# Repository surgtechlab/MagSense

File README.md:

# MagSense

Code and Library for the Leeds Surgical Technologies Lab - Magnetic Sensing Platform

Maintained by Pete Culmer

Contributions from:
******************************
Chris Adams
Max Houghton
Pete Culmer
Belquis Haider

Links:
******************************
This owes a debt to the more general purpose MLX90393 driver
https://github.com/tedyapo/arduino-MLX90393

TODO LIST
******************************
Add Bluetooth communication
 
Simplify I2C code
  ***Use wrapper function to provide a single interface to the mutliple I2C buses - for the commands below:
  Wire.beginTransmission(_I2CAddress);
  Wire.write(0x80)
  Wire.endTransmission()
  Wire.requestFrom(_I2CAddress, 1);
  Wire.available()
  Wire.read();

Add handshaking and commands to I2C comms
  Start/stop/reset/ack packet etc.
  
Improve error checking of chip configuration (check registers after config)

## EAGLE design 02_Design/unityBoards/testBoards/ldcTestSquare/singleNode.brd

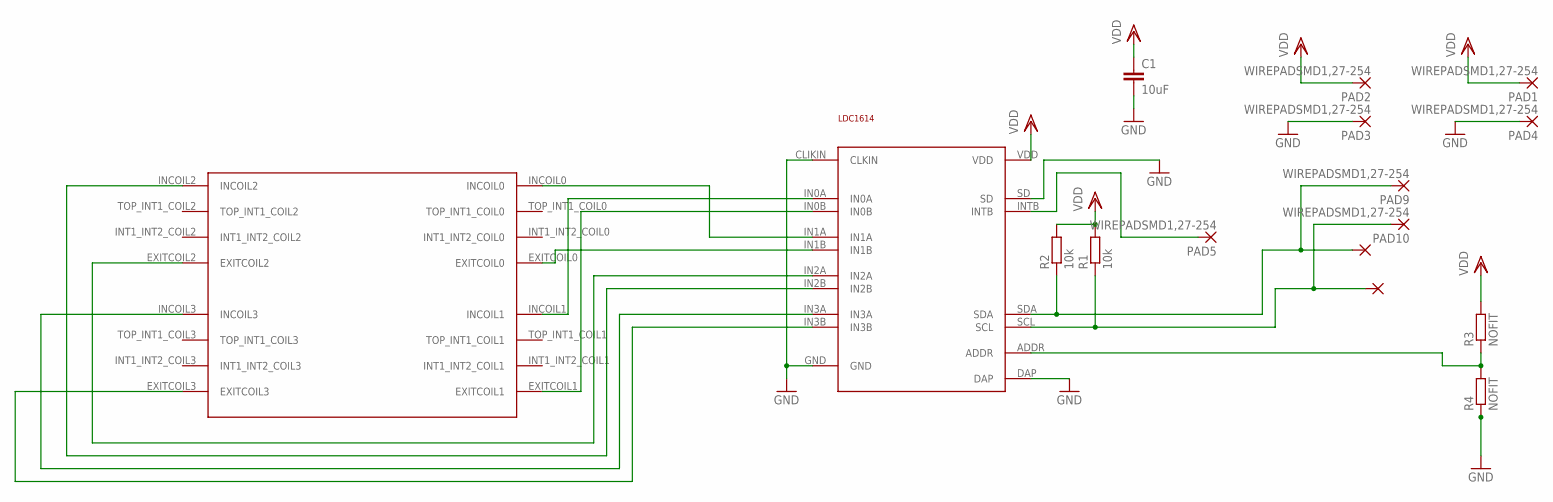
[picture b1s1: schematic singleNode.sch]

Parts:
C1: 10uF; C0402
PAD1, PAD2, PAD3, PAD4, PAD5, PAD6, PAD7, PAD9, PAD10: WIREPADSMD1,27-254; SMD1,27-2,54
R1, R2: 10k; R0402
R3, R4: NOFIT; R0201
U1: LDC1614; WQFN-16
U$2: FATSQUARE_GROUP; FAT_SQUARE

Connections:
ADDR: R3.1, R4.2, U1.ADDR
GND: C1.2, PAD3.1, PAD4.1, R4.1, U1.CLIKIN (CLKIN), U1.DAP, U1.GND, U1.SD
INTRPT: PAD5.1, U1.INTB
unnamed: U1.IN1A, U$2.INCOIL0
unnamed: U1.IN1B, U$2.EXITCOIL0
unnamed: U1.IN0A, U$2.INCOIL1
unnamed: U1.IN0B, U$2.EXITCOIL1
unnamed: U1.IN2A, U$2.EXITCOIL2
unnamed: U1.IN2B, U$2.INCOIL2
unnamed: U1.IN3A, U$2.INCOIL3
unnamed: U1.IN3B, U$2.EXITCOIL3
SCL: PAD7.1, PAD10.1, R1.1, U1.SCL
SDA: PAD6.1, PAD9.1, R2.1, U1.SDA
VDD: C1.1, PAD1.1, PAD2.1, R1.2, R2.2, R3.2, U1.VDD

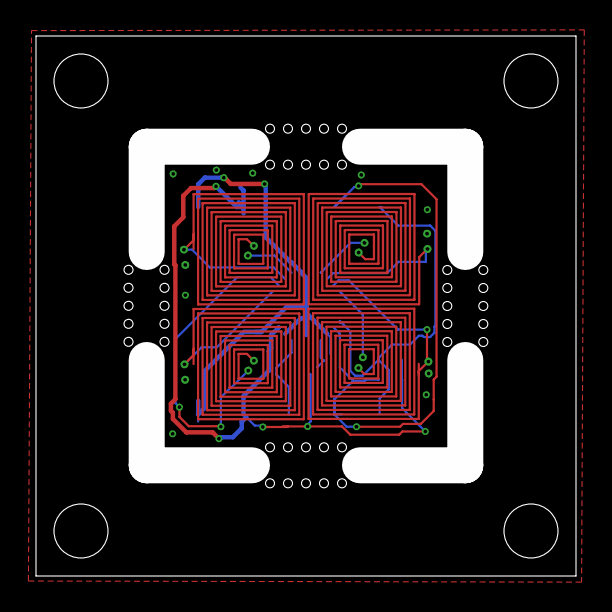
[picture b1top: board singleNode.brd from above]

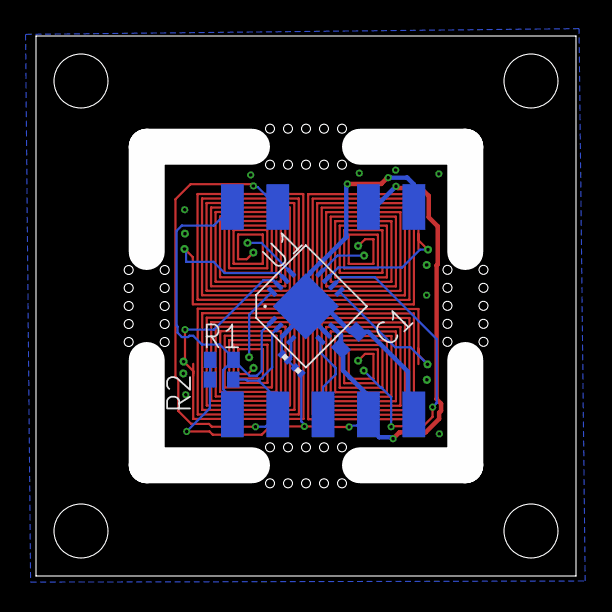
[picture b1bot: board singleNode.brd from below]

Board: 4 copper layers, 30.0 x 30.0 mm, 16 parts (15 on the bottom side), 14 nets.

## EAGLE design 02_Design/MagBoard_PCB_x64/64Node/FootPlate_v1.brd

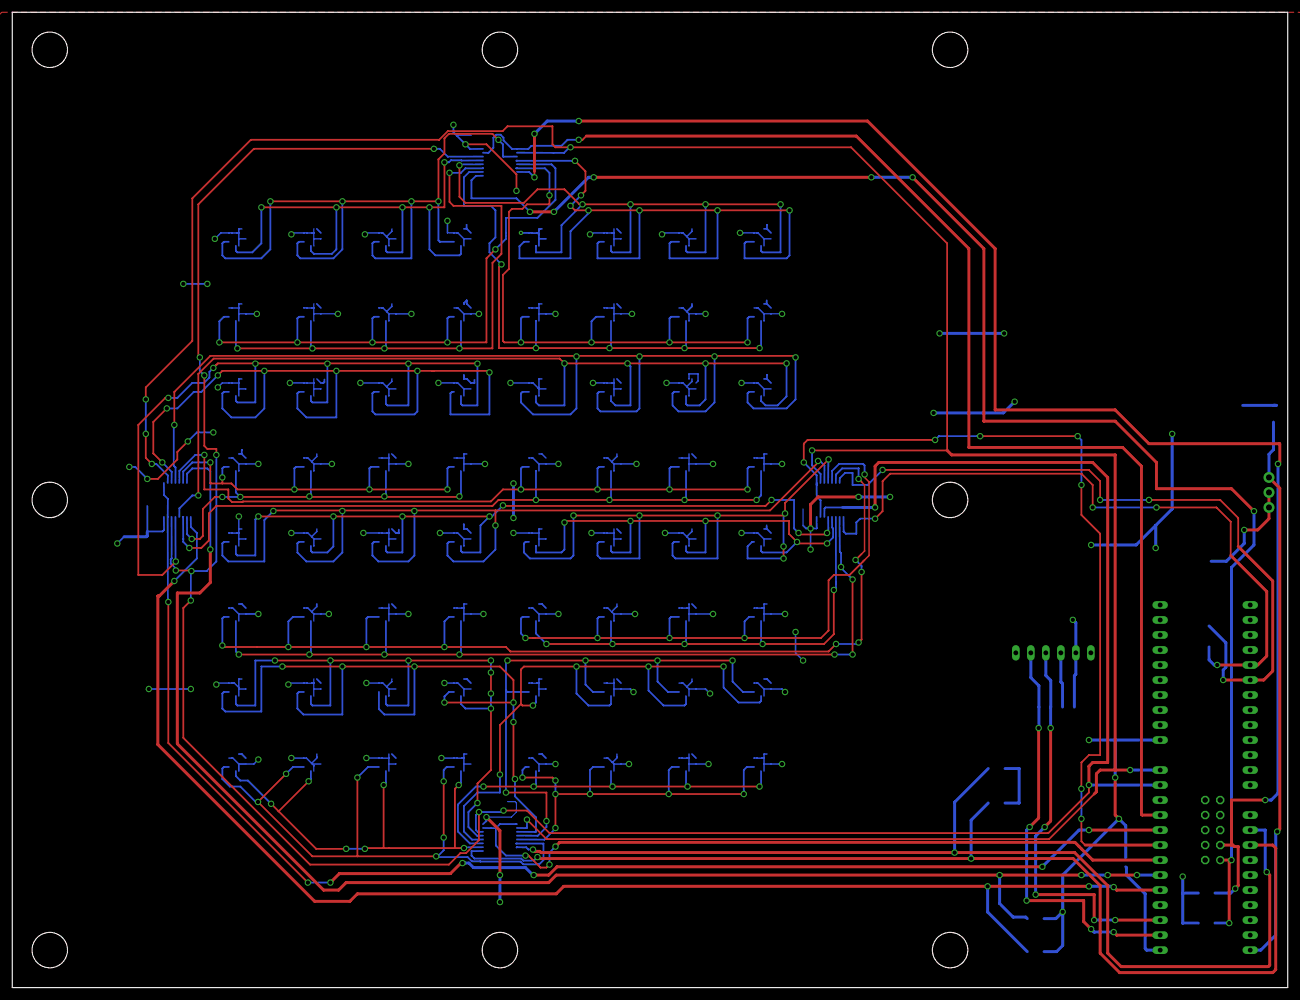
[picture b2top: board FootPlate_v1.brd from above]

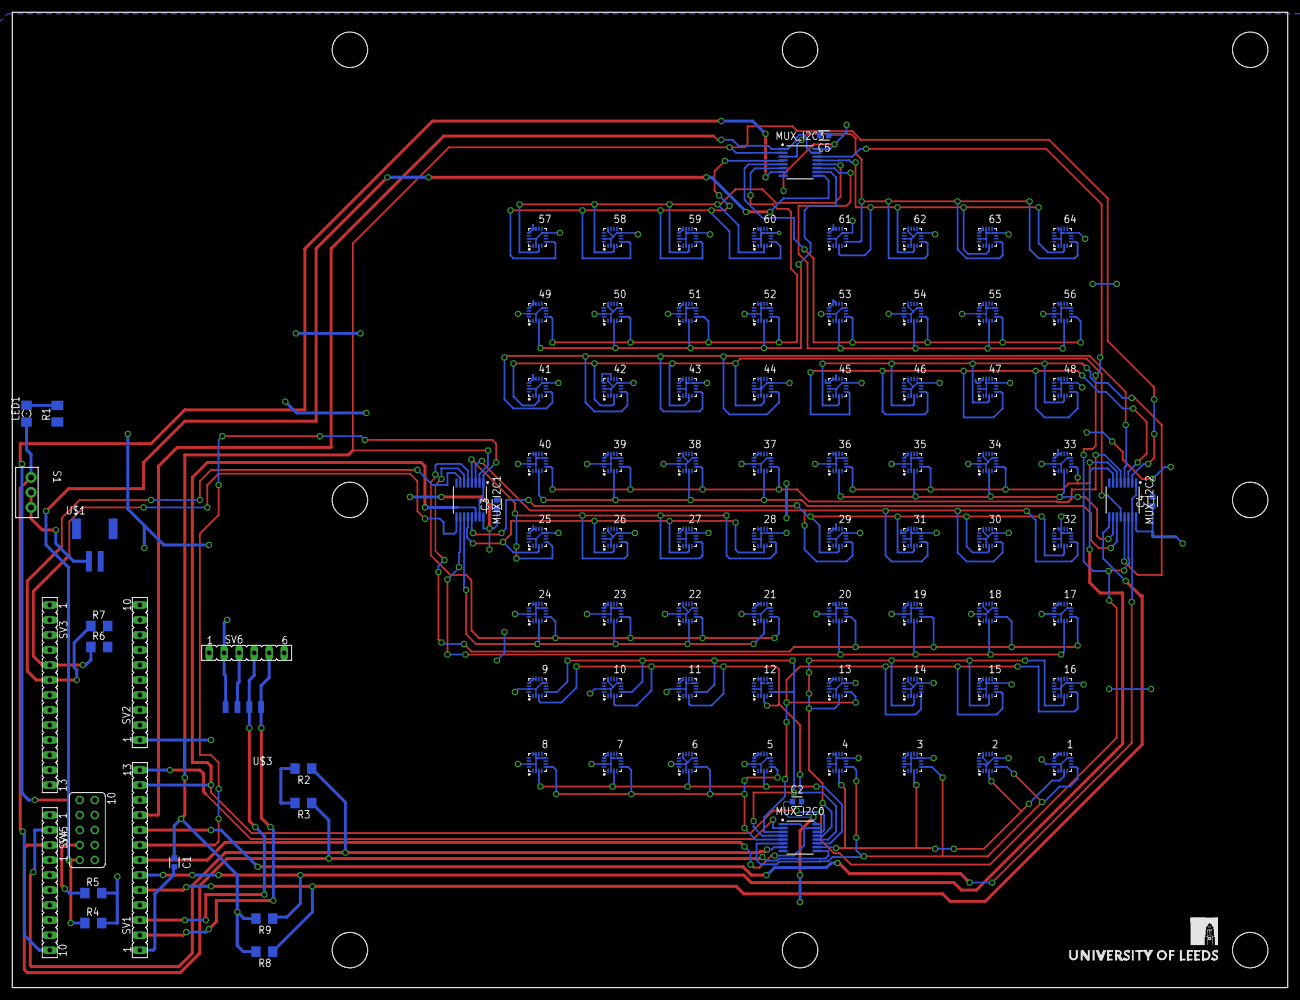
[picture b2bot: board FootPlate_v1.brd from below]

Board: 2 copper layers, 215.9 x 165.1 mm, 93 parts (93 on the bottom side), 53 nets.

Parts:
1, 5, 9, 13, 17, 21, 25, 29, 33, 37, 41, 45, 49, 53, 57, 61: 0x00; MLX90393_PKG
2, 6, 10, 14, 18, 22, 26, 30, 34, 38, 42, 46, 50, 54, 58, 62: 0x01; MLX90393_PKG
3, 7, 11, 15, 19, 23, 27, 31, 35, 39, 43, 47, 51, 55, 59, 63: 0x10; MLX90393_PKG
4, 8, 12, 16, 20, 24, 28, 32, 36, 40, 44, 48, 52, 56, 60, 64: 0x11; MLX90393_PKG
C1, C2, C3, C4, C5: 0.1uF; CAPC1608X75
LED1: 1206
MUX_I2C0, MUX_I2C1, MUX_I2C2, MUX_I2C3: SN74_MUXMUX_PKG_V2; SOP65P640X120-16
R1: 80 Ohm; M1206
R2, R3, R4, R5, R6, R7, R8, R9: 4.7k; R1206
S1: SWITCH
SV1, SV3: FE13
SV2, SV4: FE10
SV5: FE05-2
SV6: FE06
U$1: JST_CONNECTOR; JST_PKG
U$2: LOGO_LARGE
U$3: 90DEG_F_HEADER; 90DEG_F_HEADER_PKG

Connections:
!OE0: MUX_I2C0.!1OE, MUX_I2C0.!2OE, SV1.7
!OE1: MUX_I2C1.!1OE, MUX_I2C1.!2OE, SV1.8
!OE2: MUX_I2C2.!1OE, MUX_I2C2.!2OE, SV1.9
!OE3: MUX_I2C3.!1OE, MUX_I2C3.!2OE, SV1.10
+3.7V: LED1.A, S1.1, SV4.10
BT_RX: SV1.2, SV6.5, U$3.1
BT_TX: SV1.3, SV6.4, U$3.2
GND: 1.A0, 1.A1, 1.VSS, 2.A1, 2.VSS, 3.A0, 3.VSS, 4.VSS, 5.A0, 5.A1, 5.VSS, 6.A1, 6.VSS, 7.A0, 7.VSS, 8.VSS, 9.A0, 9.A1, 9.VSS, 10.A1, 10.VSS, 11.A0, 11.VSS, 12.VSS, 13.A0, 13.A1, 13.VSS, 14.A1, 14.VSS, 15.A0, 15.VSS, 16.VSS, 17.A0, 17.A1, 17.VSS, 18.A1, 18.VSS, 19.A0, 19.VSS, 20.VSS, 21.A0, 21.A1, 21.VSS, 22.A1, 22.VSS, 23.A0, 23.VSS, 24.VSS, 25.A0, 25.A1, 25.VSS, 26.A1, 26.VSS, 27.A0, 27.VSS, 28.VSS, 29.A0, 29.A1, 29.VSS, 30.A1, 30.VSS, 31.A0, 31.VSS, 32.VSS, 33.A0, 33.A1, 33.VSS, 34.A1, 34.VSS, 35.A0, 35.VSS, 36.VSS, 37.A0, 37.A1, 37.VSS, 38.A1, 38.VSS, 39.A0, 39.VSS, 40.VSS, 41.A0, 41.A1, 41.VSS, 42.A1, 42.VSS, 43.A0, 43.VSS, 44.VSS, 45.A0, 45.A1, 45.VSS, 46.A1, 46.VSS, 47.A0, 47.VSS, 48.VSS, 49.A0, 49.A1, 49.VSS, 50.A1, 50.VSS, 51.A0, 51.VSS, 52.VSS, 53.A0, 53.A1, 53.VSS, 54.A1, 54.VSS, 55.A0, 55.VSS, 56.VSS, 57.A0, 57.A1, 57.VSS, 58.A1, 58.VSS, 59.A0, 59.VSS, 60.VSS, 61.A0, 61.A1, 61.VSS, 62.A1, 62.VSS, 63.A0, 63.VSS, 64.VSS, C1.2, C2.2, C3.2, C4.2, C5.2, MUX_I2C0.GND, MUX_I2C1.GND, MUX_I2C2.GND, MUX_I2C3.GND, R1.1, SV1.1, SV3.10, SV4.9, SV6.3, U$1.GND, U$3.3
unnamed: LED1.C, R1.2
unnamed: S1.2, S1.3, U$1.+3.7V
S0: MUX_I2C0.S0, MUX_I2C1.S0, MUX_I2C2.S0, MUX_I2C3.S0, SV1.12
S1: MUX_I2C0.S1, MUX_I2C1.S1, MUX_I2C2.S1, MUX_I2C3.S1, SV1.13
SCL0: MUX_I2C0.2A, R3.1, SV4.3
SCL0_0: 1.SCL, 2.SCL, 3.SCL, 4.SCL, MUX_I2C0.2B1
SCL0_1: 5.SCL, 6.SCL, 7.SCL, 8.SCL, MUX_I2C0.2B2
SCL0_2: 9.SCL, 10.SCL, 11.SCL, 12.SCL, MUX_I2C0.2B3
SCL0_3: 13.SCL, 14.SCL, 15.SCL, 16.SCL, MUX_I2C0.2B4
SCL1: MUX_I2C1.2A, R6.1, SV3.5
SCL1_0: 17.SCL, 18.SCL, 19.SCL, 20.SCL, MUX_I2C1.2B1
SCL1_1: 21.SCL, 22.SCL, 23.SCL, 24.SCL, MUX_I2C1.2B2
SCL1_2: 25.SCL, 26.SCL, 27.SCL, 28.SCL, MUX_I2C1.2B3
SCL1_3: 29.SCL, 30.SCL, 31.SCL, 32.SCL, MUX_I2C1.2B4
SCL2: MUX_I2C2.2A, R8.1, SV1.5
SCL2_0: 33.SCL, 34.SCL, 35.SCL, 36.SCL, MUX_I2C2.2B1
SCL2_1: 37.SCL, 38.SCL, 39.SCL, 40.SCL, MUX_I2C2.2B2
SCL2_2: 41.SCL, 42.SCL, 43.SCL, 44.SCL, MUX_I2C2.2B3
SCL2_3: 45.SCL, 46.SCL, 47.SCL, 48.SCL, MUX_I2C2.2B4
SCL3: MUX_I2C3.2A, R4.1, SV5.1
SCL3_0: 49.SCL, 50.SCL, 51.SCL, 52.SCL, MUX_I2C3.2B1
SCL3_1: 53.SCL, 54.SCL, 55.SCL, 56.SCL, MUX_I2C3.2B2
SCL3_2: 57.SCL, 58.SCL, 59.SCL, 60.SCL, MUX_I2C3.2B3
SCL3_3: 61.SCL, 62.SCL, 63.SCL, 64.SCL, MUX_I2C3.2B4
SDA0: MUX_I2C0.1A, R2.1, SV4.2
SDA0_0: 1.SDA, 2.SDA, 3.SDA, 4.SDA, MUX_I2C0.1B1
SDA0_1: 5.SDA, 6.SDA, 7.SDA, 8.SDA, MUX_I2C0.1B2
SDA0_2: 9.SDA, 10.SDA, 11.SDA, 12.SDA, MUX_I2C0.1B3
SDA0_3: 13.SDA, 14.SDA, 15.SDA, 16.SDA, MUX_I2C0.1B4
SDA1: MUX_I2C1.1A, R7.1, SV3.6
SDA1_0: 17.SDA, 18.SDA, 19.SDA, 20.SDA, MUX_I2C1.1B1
SDA1_1: 21.SDA, 22.SDA, 23.SDA, 24.SDA, MUX_I2C1.1B2
SDA1_2: 25.SDA, 26.SDA, 27.SDA, 28.SDA, MUX_I2C1.1B3
SDA1_3: 29.SDA, 30.SDA, 31.SDA, 32.SDA, MUX_I2C1.1B4
SDA2: MUX_I2C2.1A, R9.1, SV1.6
SDA2_0: 33.SDA, 34.SDA, 35.SDA, 36.SDA, MUX_I2C2.1B1
SDA2_1: 37.SDA, 38.SDA, 39.SDA, 40.SDA, MUX_I2C2.1B2
SDA2_2: 41.SDA, 42.SDA, 43.SDA, 44.SDA, MUX_I2C2.1B3
SDA2_3: 45.SDA, 46.SDA, 47.SDA, 48.SDA, MUX_I2C2.1B4
SDA3: MUX_I2C3.1A, R5.1, SV5.3
SDA3_0: 49.SDA, 50.SDA, 51.SDA, 52.SDA, MUX_I2C3.1B1
SDA3_1: 53.SDA, 54.SDA, 55.SDA, 56.SDA, MUX_I2C3.1B2
SDA3_2: 57.SDA, 58.SDA, 59.SDA, 60.SDA, MUX_I2C3.1B3
SDA3_3: 61.SDA, 62.SDA, 63.SDA, 64.SDA, MUX_I2C3.1B4
VDD: 1.SENB/CS, 1.VDD, 1.VDD_IO, 2.A0, 2.SENB/CS, 2.VDD, 2.VDD_IO, 3.A1, 3.SENB/CS, 3.VDD, 3.VDD_IO, 4.A0, 4.A1, 4.SENB/CS, 4.VDD, 4.VDD_IO, 5.SENB/CS, 5.VDD, 5.VDD_IO, 6.A0, 6.SENB/CS, 6.VDD, 6.VDD_IO, 7.A1, 7.SENB/CS, 7.VDD, 7.VDD_IO, 8.A0, 8.A1, 8.SENB/CS, 8.VDD, 8.VDD_IO, 9.SENB/CS, 9.VDD, 9.VDD_IO, 10.A0, 10.SENB/CS, 10.VDD, 10.VDD_IO, 11.A1, 11.SENB/CS, 11.VDD, 11.VDD_IO, 12.A0, 12.A1, 12.SENB/CS, 12.VDD, 12.VDD_IO, 13.SENB/CS, 13.VDD, 13.VDD_IO, 14.A0, 14.SENB/CS, 14.VDD, 14.VDD_IO, 15.A1, 15.SENB/CS, 15.VDD, 15.VDD_IO, 16.A0, 16.A1, 16.SENB/CS, 16.VDD, 16.VDD_IO, 17.SENB/CS, 17.VDD, 17.VDD_IO, 18.A0, 18.SENB/CS, 18.VDD, 18.VDD_IO, 19.A1, 19.SENB/CS, 19.VDD, 19.VDD_IO, 20.A0, 20.A1, 20.SENB/CS, 20.VDD, 20.VDD_IO, 21.SENB/CS, 21.VDD, 21.VDD_IO, 22.A0, 22.SENB/CS, 22.VDD, 22.VDD_IO, 23.A1, 23.SENB/CS, 23.VDD, 23.VDD_IO, 24.A0, 24.A1, 24.SENB/CS, 24.VDD, 24.VDD_IO, 25.SENB/CS, 25.VDD, 25.VDD_IO, 26.A0, 26.SENB/CS, 26.VDD, 26.VDD_IO, 27.A1, 27.SENB/CS, 27.VDD, 27.VDD_IO, 28.A0, 28.A1, 28.SENB/CS, 28.VDD, 28.VDD_IO, 29.SENB/CS, 29.VDD, 29.VDD_IO, 30.A0, 30.SENB/CS, 30.VDD, 30.VDD_IO, 31.A1, 31.SENB/CS, 31.VDD, 31.VDD_IO, 32.A0, 32.A1, 32.SENB/CS, 32.VDD, 32.VDD_IO, 33.SENB/CS, 33.VDD, 33.VDD_IO, 34.A0, 34.SENB/CS, 34.VDD, 34.VDD_IO, 35.A1, 35.SENB/CS, 35.VDD, 35.VDD_IO, 36.A0, 36.A1, 36.SENB/CS, 36.VDD, 36.VDD_IO, 37.SENB/CS, 37.VDD, 37.VDD_IO, 38.A0, 38.SENB/CS, 38.VDD, 38.VDD_IO, 39.A1, 39.SENB/CS, 39.VDD, 39.VDD_IO, 40.A0, 40.A1, 40.SENB/CS, 40.VDD, 40.VDD_IO, 41.SENB/CS, 41.VDD, 41.VDD_IO, 42.A0, 42.SENB/CS, 42.VDD, 42.VDD_IO, 43.A1, 43.SENB/CS, 43.VDD, 43.VDD_IO, 44.A0, 44.A1, 44.SENB/CS, 44.VDD, 44.VDD_IO, 45.SENB/CS, 45.VDD, 45.VDD_IO, 46.A0, 46.SENB/CS, 46.VDD, 46.VDD_IO, 47.A1, 47.SENB/CS, 47.VDD, 47.VDD_IO, 48.A0, 48.A1, 48.SENB/CS, 48.VDD, 48.VDD_IO, 49.SENB/CS, 49.VDD, 49.VDD_IO, 50.A0, 50.SENB/CS, 50.VDD, 50.VDD_IO, 51.A1, 51.SENB/CS, 51.VDD, 51.VDD_IO, 52.A0, 52.A1, 52.SENB/CS, 52.VDD, 52.VDD_IO, 53.SENB/CS, 53.VDD, 53.VDD_IO, 54.A0, 54.SENB/CS, 54.VDD, 54.VDD_IO, 55.A1, 55.SENB/CS, 55.VDD, 55.VDD_IO, 56.A0, 56.A1, 56.SENB/CS, 56.VDD, 56.VDD_IO, 57.SENB/CS, 57.VDD, 57.VDD_IO, 58.A0, 58.SENB/CS, 58.VDD, 58.VDD_IO, 59.A1, 59.SENB/CS, 59.VDD, 59.VDD_IO, 60.A0, 60.A1, 60.SENB/CS, 60.VDD, 60.VDD_IO, 61.SENB/CS, 61.VDD, 61.VDD_IO, 62.A0, 62.SENB/CS, 62.VDD, 62.VDD_IO, 63.A1, 63.SENB/CS, 63.VDD, 63.VDD_IO, 64.A0, 64.A1, 64.SENB/CS, 64.VDD, 64.VDD_IO, C1.1, C2.1, C3.1, C4.1, C5.1, MUX_I2C0.VCC, MUX_I2C1.VCC, MUX_I2C2.VCC, MUX_I2C3.VCC, R2.2, R3.2, R4.2, R5.2, R6.2, R7.2, R8.2, R9.2, SV2.1, SV6.2, U$3.4

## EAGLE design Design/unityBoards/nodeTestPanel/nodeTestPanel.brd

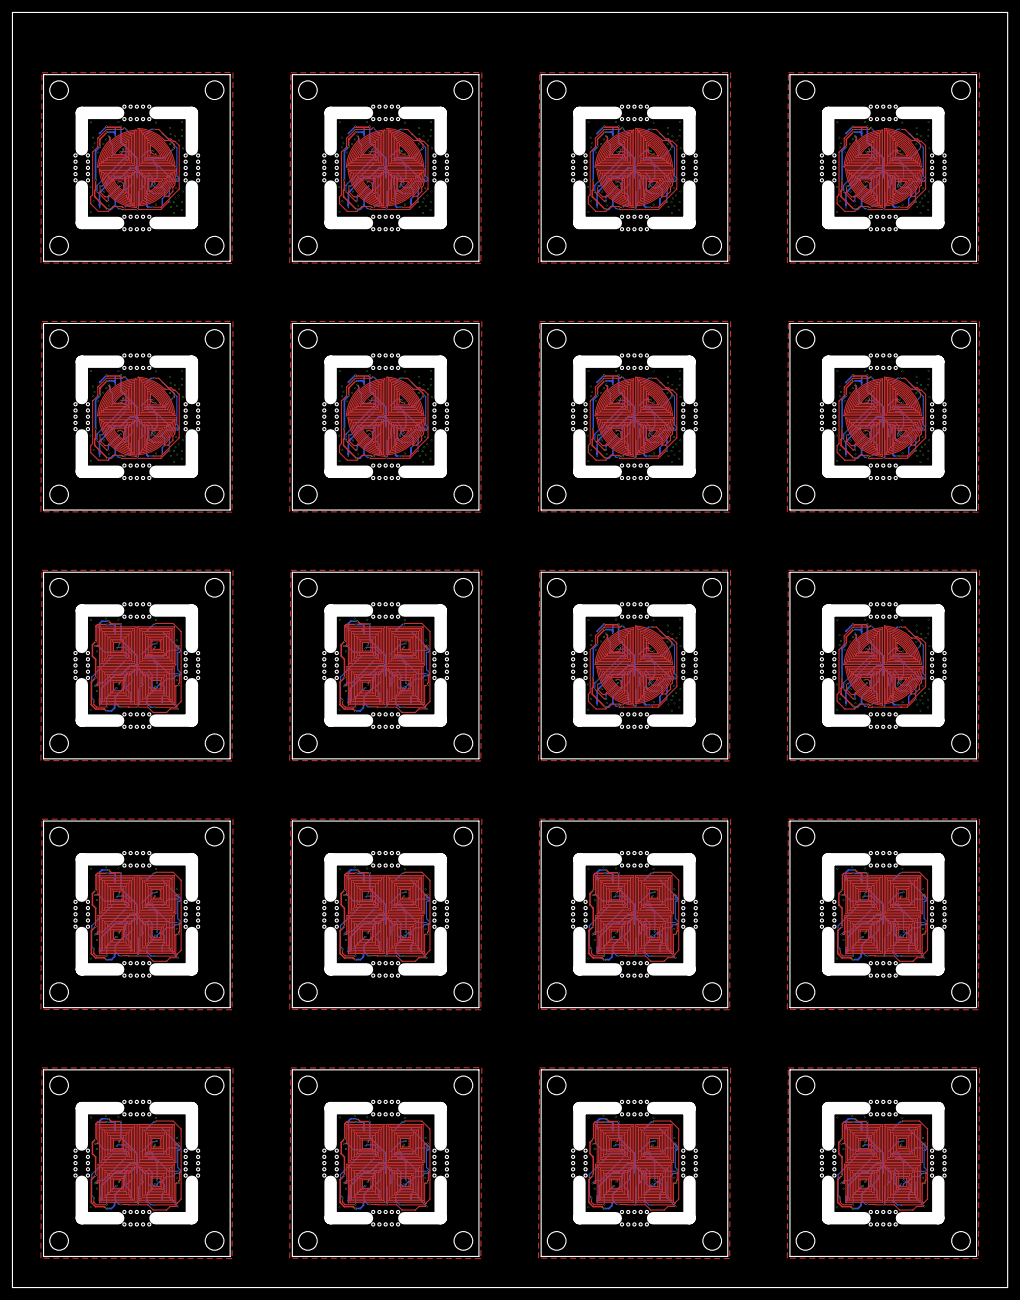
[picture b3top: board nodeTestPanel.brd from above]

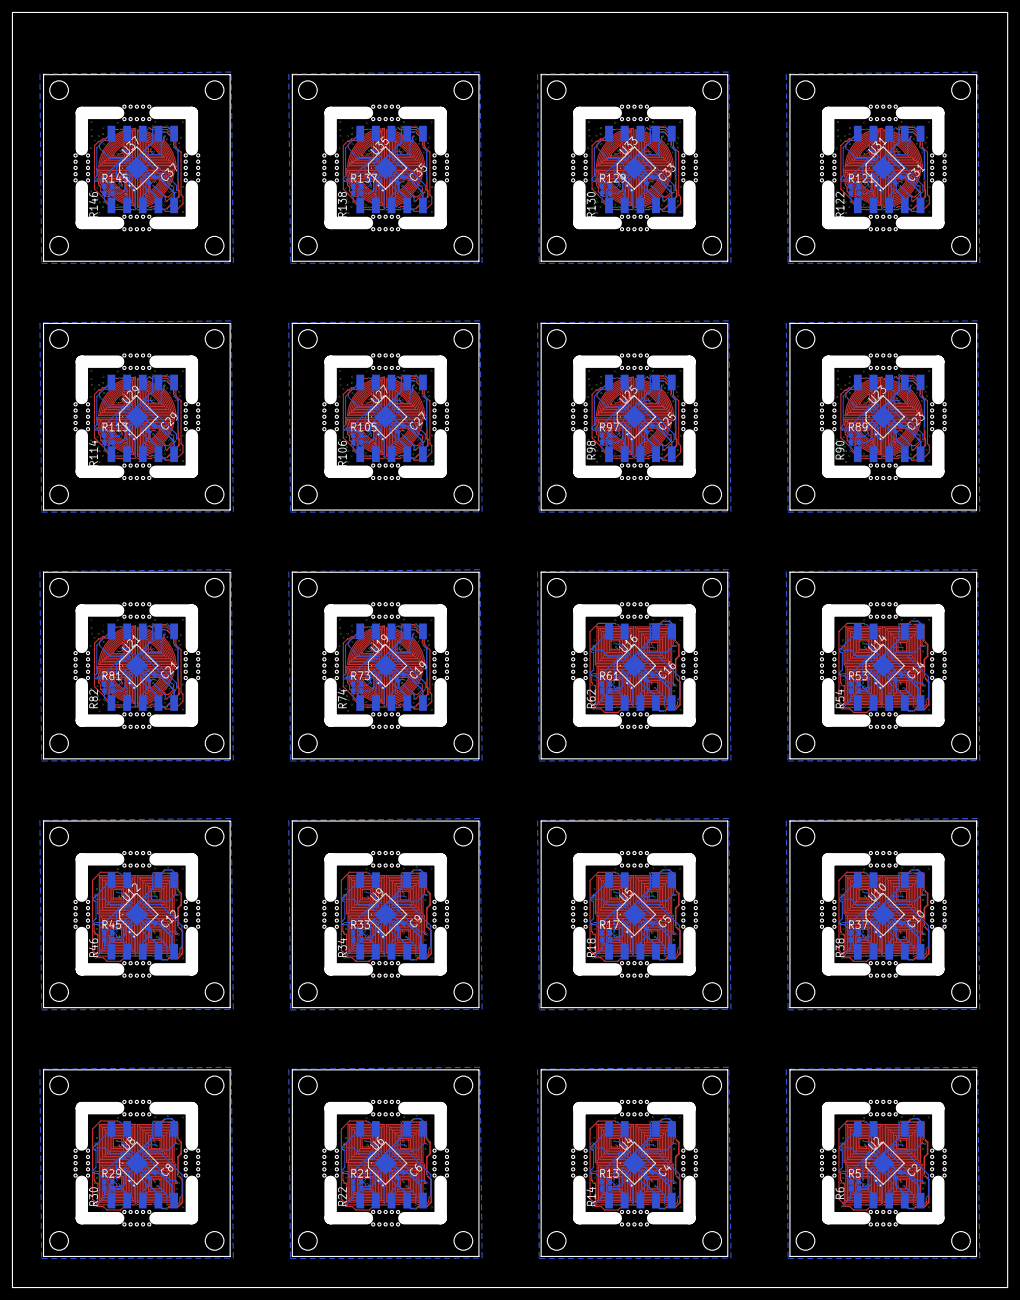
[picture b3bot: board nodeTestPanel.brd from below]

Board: 4 copper layers, 160.0 x 205.0 mm, 330 parts (310 on the bottom side), 242 nets.

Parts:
C2, C4, C5, C6, C8, C9, C10, C12, C14, C16, C19, C21, C23, C25, C27, C29, C31, C33, C35, C37: 10uF; C0402
PAD8, PAD11, PAD12, PAD13, PAD14, PAD15, PAD16, PAD17, PAD18, PAD28, PAD29, PAD30, PAD31, PAD32, PAD33, PAD34, PAD35, PAD36, PAD37, PAD38, PAD39, PAD40, PAD41, PAD42, PAD43, PAD44, PAD45, PAD46, PAD47, PAD48, PAD49, PAD50, PAD51, PAD52, PAD53, PAD54, PAD64, PAD65, PAD66, PAD67, PAD68, PAD69, PAD70, PAD71, PAD72, PAD73, PAD74, PAD75, PAD76, PAD77, PAD78, PAD79, PAD80, PAD81, PAD82, PAD83, PAD84, PAD85, PAD86, PAD87, PAD88, PAD89, PAD90, PAD100, PAD101, PAD102, PAD103, PAD104, PAD105, PAD106, PAD107, PAD108, PAD118, PAD119, PAD120, PAD121, PAD122, PAD123, PAD124, PAD125, PAD126, PAD136, PAD137, PAD138, PAD139, PAD140, PAD141, PAD142, PAD143, PAD144, PAD165, PAD166, PAD167, PAD168, PAD169, PAD170, PAD171, PAD172, PAD173, PAD174, PAD185, PAD186, PAD187, PAD188, PAD189, PAD190, PAD191, PAD192, PAD193, PAD194, PAD205, PAD206, PAD207, PAD208, PAD209, PAD210, PAD211, PAD212, PAD213, PAD214, PAD225, PAD226, PAD227, PAD228, PAD229, PAD230, PAD231, PAD232, PAD233, PAD234, PAD245, PAD246, PAD247, PAD248, PAD249, PAD250, PAD251, PAD252, PAD253, PAD254, PAD265, PAD266, PAD267, PAD268, PAD269, PAD270, PAD271, PAD272, PAD273, PAD274, PAD285, PAD286, PAD287, PAD288, PAD289, PAD290, PAD291, PAD292, PAD293, PAD294, PAD305, PAD306, PAD307, PAD308, PAD309, PAD310, PAD311, PAD312, PAD313, PAD314, PAD325, PAD326, PAD327, PAD328, PAD329, PAD330, PAD331, PAD332, PAD333, PAD334, PAD345, PAD346, PAD347, PAD348, PAD349, PAD350, PAD351, PAD352, PAD353, PAD354: WIREPADSMD1,27-254; SMD1,27-2,54
R5, R6, R13, R14, R17, R18, R21, R22, R29, R30, R33, R34, R37, R38, R45, R46, R53, R54, R61, R62, R73, R74, R81, R82, R89, R90, R97, R98, R105, R106, R113, R114, R121, R122, R129, R130, R137, R138, R145, R146: 10k; R0402
R7, R8, R15, R16, R19, R20, R23, R24, R31, R32, R35, R36, R39, R40, R47, R48, R55, R56, R63, R64, R75, R76, R83, R84, R91, R92, R99, R100, R107, R108, R115, R116, R123, R124, R131, R132, R139, R140, R147, R148: NOFIT; R0201
U2, U4, U5, U6, U8, U9, U10, U12, U14, U16, U19, U21, U23, U25, U27, U29, U31, U33, U35, U37: LDC1614; WQFN-16
U$1, U$4, U$5, U$6, U$8, U$9, U$10, U$12, U$14, U$16: FATSQUARE_GROUP; FAT_SQUARE
U$19, U$21, U$23, U$25, U$27, U$29, U$31, U$33, U$35, U$37: FATFAN_GROUP; FAT_FAN

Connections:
ADDR1: R7.1, R8.2, U2.ADDR
ADDR3: R15.1, R16.2, U4.ADDR
ADDR4: R19.1, R20.2, U5.ADDR
ADDR5: R23.1, R24.2, U6.ADDR
ADDR7: R31.1, R32.2, U8.ADDR
ADDR8: R35.1, R36.2, U9.ADDR
ADDR9: R39.1, R40.2, U10.ADDR
ADDR11: R47.1, R48.2, U12.ADDR
ADDR13: R55.1, R56.2, U14.ADDR
ADDR15: R63.1, R64.2, U16.ADDR
ADDR18: R75.1, R76.2, U19.ADDR
ADDR20: R83.1, R84.2, U21.ADDR
ADDR22: R91.1, R92.2, U23.ADDR
ADDR24: R99.1, R100.2, U25.ADDR
ADDR26: R107.1, R108.2, U27.ADDR
ADDR28: R115.1, R116.2, U29.ADDR
ADDR30: R123.1, R124.2, U31.ADDR
ADDR32: R131.1, R132.2, U33.ADDR
ADDR34: R139.1, R140.2, U35.ADDR
ADDR36: R147.1, R148.2, U37.ADDR
GND: C2.2, C4.2, C5.2, C6.2, C8.2, C9.2, C10.2, C12.2, C14.2, C16.2, C19.2, C21.2, C23.2, C25.2, C27.2, C29.2, C31.2, C33.2, C35.2, C37.2, PAD11.1, PAD16.1, PAD29.1, PAD34.1, PAD38.1, PAD43.1, PAD47.1, PAD52.1, PAD65.1, PAD70.1, PAD74.1, PAD79.1, PAD83.1, PAD88.1, PAD101.1, PAD106.1, PAD119.1, PAD124.1, PAD137.1, PAD142.1, PAD166.1, PAD171.1, PAD186.1, PAD191.1, PAD206.1, PAD211.1, PAD226.1, PAD231.1, PAD246.1, PAD251.1, PAD266.1, PAD271.1, PAD286.1, PAD291.1, PAD306.1, PAD311.1, PAD326.1, PAD331.1, PAD346.1, PAD351.1, R8.1, R16.1, R20.1, R24.1, R32.1, R36.1, R40.1, R48.1, R56.1, R64.1, R76.1, R84.1, R92.1, R100.1, R108.1, R116.1, R124.1, R132.1, R140.1, R148.1, U2.CLIKIN, U2.DAP, U2.GND, U2.SD, U4.CLIKIN, U4.DAP, U4.GND, U4.SD, U5.CLIKIN, U5.DAP, U5.GND, U5.SD, U6.CLIKIN, U6.DAP, U6.GND, U6.SD, U8.CLIKIN, U8.DAP, U8.GND, U8.SD, U9.CLIKIN, U9.DAP, U9.GND, U9.SD, U10.CLIKIN, U10.DAP, U10.GND, U10.SD, U12.CLIKIN, U12.DAP, U12.GND, U12.SD, U14.CLIKIN, U14.DAP, U14.GND, U14.SD, U16.CLIKIN, U16.DAP, U16.GND, U16.SD, U19.CLIKIN, U19.DAP, U19.GND, U19.SD, U21.CLIKIN, U21.DAP, U21.GND, U21.SD, U23.CLIKIN, U23.DAP, U23.GND, U23.SD, U25.CLIKIN, U25.DAP, U25.GND, U25.SD, U27.CLIKIN, U27.DAP, U27.GND, U27.SD, U29.CLIKIN, U29.DAP, U29.GND, U29.SD, U31.CLIKIN, U31.DAP, U31.GND, U31.SD, U33.CLIKIN, U33.DAP, U33.GND, U33.SD, U35.CLIKIN, U35.DAP, U35.GND, U35.SD, U37.CLIKIN, U37.DAP, U37.GND, U37.SD
INTRPT1: PAD12.1, U2.INTB
INTRPT3: PAD30.1, U4.INTB
INTRPT4: PAD39.1, U5.INTB
INTRPT5: PAD48.1, U6.INTB
INTRPT7: PAD66.1, U8.INTB
INTRPT8: PAD75.1, U9.INTB
INTRPT9: PAD84.1, U10.INTB
INTRPT11: PAD102.1, U12.INTB
INTRPT13: PAD120.1, U14.INTB
INTRPT15: PAD138.1, U16.INTB
INTRPT18: PAD167.1, PAD172.1, U19.INTB
INTRPT20: PAD187.1, PAD192.1, U21.INTB
INTRPT22: PAD207.1, PAD212.1, U23.INTB
INTRPT24: PAD227.1, PAD232.1, U25.INTB
INTRPT26: PAD247.1, PAD252.1, U27.INTB
INTRPT28: PAD267.1, PAD272.1, U29.INTB
INTRPT30: PAD287.1, PAD292.1, U31.INTB
INTRPT32: PAD307.1, PAD312.1, U33.INTB
INTRPT34: PAD327.1, PAD332.1, U35.INTB
INTRPT36: PAD347.1, PAD352.1, U37.INTB
unnamed: U2.IN1B, U$1.EXITCOIL0
unnamed: U2.IN0A, U$1.INCOIL1
unnamed: U2.IN0B, U$1.EXITCOIL1
unnamed: U2.IN2A, U$1.EXITCOIL2
unnamed: U2.IN2B, U$1.INCOIL2
unnamed: U2.IN3A, U$1.INCOIL3
unnamed: U2.IN3B, U$1.EXITCOIL3
unnamed: U2.IN1A, U$1.INCOIL0
unnamed: U4.IN1B, U$4.EXITCOIL0
unnamed: U4.IN0A, U$4.INCOIL1
unnamed: U4.IN0B, U$4.EXITCOIL1
unnamed: U4.IN2A, U$4.EXITCOIL2
unnamed: U4.IN2B, U$4.INCOIL2
unnamed: U4.IN3A, U$4.INCOIL3
unnamed: U4.IN3B, U$4.EXITCOIL3
unnamed: U4.IN1A, U$4.INCOIL0
unnamed: U5.IN1B, U$5.EXITCOIL0
unnamed: U5.IN0A, U$5.INCOIL1
unnamed: U5.IN0B, U$5.EXITCOIL1
unnamed: U5.IN2A, U$5.EXITCOIL2
unnamed: U5.IN2B, U$5.INCOIL2
unnamed: U5.IN3A, U$5.INCOIL3
unnamed: U5.IN3B, U$5.EXITCOIL3
unnamed: U5.IN1A, U$5.INCOIL0
unnamed: U6.IN1B, U$6.EXITCOIL0
unnamed: U6.IN0A, U$6.INCOIL1
unnamed: U6.IN0B, U$6.EXITCOIL1
unnamed: U6.IN2A, U$6.EXITCOIL2
unnamed: U6.IN2B, U$6.INCOIL2
unnamed: U6.IN3A, U$6.INCOIL3
unnamed: U6.IN3B, U$6.EXITCOIL3
unnamed: U6.IN1A, U$6.INCOIL0
unnamed: U8.IN1B, U$8.EXITCOIL0
unnamed: U8.IN0A, U$8.INCOIL1
unnamed: U8.IN0B, U$8.EXITCOIL1
unnamed: U8.IN2A, U$8.EXITCOIL2
unnamed: U8.IN2B, U$8.INCOIL2
unnamed: U8.IN3A, U$8.INCOIL3
unnamed: U8.IN3B, U$8.EXITCOIL3
unnamed: U8.IN1A, U$8.INCOIL0
unnamed: U9.IN1B, U$9.EXITCOIL0
unnamed: U9.IN0A, U$9.INCOIL1
unnamed: U9.IN0B, U$9.EXITCOIL1
unnamed: U9.IN2A, U$9.EXITCOIL2
unnamed: U9.IN2B, U$9.INCOIL2
unnamed: U9.IN3A, U$9.INCOIL3
unnamed: U9.IN3B, U$9.EXITCOIL3
unnamed: U9.IN1A, U$9.INCOIL0
unnamed: U10.IN1B, U$10.EXITCOIL0
unnamed: U10.IN0A, U$10.INCOIL1
unnamed: U10.IN0B, U$10.EXITCOIL1
unnamed: U10.IN2A, U$10.EXITCOIL2
unnamed: U10.IN2B, U$10.INCOIL2
unnamed: U10.IN3A, U$10.INCOIL3
unnamed: U10.IN3B, U$10.EXITCOIL3
unnamed: U10.IN1A, U$10.INCOIL0
unnamed: U12.IN1B, U$12.EXITCOIL0
unnamed: U12.IN0A, U$12.INCOIL1
unnamed: U12.IN0B, U$12.EXITCOIL1
unnamed: U12.IN2A, U$12.EXITCOIL2
unnamed: U12.IN2B, U$12.INCOIL2
unnamed: U12.IN3A, U$12.INCOIL3
unnamed: U12.IN3B, U$12.EXITCOIL3
unnamed: U12.IN1A, U$12.INCOIL0
unnamed: U14.IN1B, U$14.EXITCOIL0
unnamed: U14.IN0A, U$14.INCOIL1
unnamed: U14.IN0B, U$14.EXITCOIL1
unnamed: U14.IN2A, U$14.EXITCOIL2
unnamed: U14.IN2B, U$14.INCOIL2
unnamed: U14.IN3A, U$14.INCOIL3
unnamed: U14.IN3B, U$14.EXITCOIL3
unnamed: U14.IN1A, U$14.INCOIL0
unnamed: U16.IN1B, U$16.EXITCOIL0
unnamed: U16.IN0A, U$16.INCOIL1
unnamed: U16.IN0B, U$16.EXITCOIL1
unnamed: U16.IN2A, U$16.EXITCOIL2
unnamed: U16.IN2B, U$16.INCOIL2
unnamed: U16.IN3A, U$16.INCOIL3
unnamed: U16.IN3B, U$16.EXITCOIL3
unnamed: U16.IN1A, U$16.INCOIL0
unnamed: U19.IN1B, U$19.EXITCOIL0
unnamed: U19.IN0A, U$19.INCOIL1
unnamed: U19.IN0B, U$19.EXITCOIL1
unnamed: U19.IN2A, U$19.EXITCOIL2B
unnamed: U19.IN2B, U$19.INCOIL2B
unnamed: U19.IN3A, U$19.INCOIL3
unnamed: U19.IN3B, U$19.EXITCOIL3
unnamed: U19.IN1A, U$19.INCOIL0
unnamed: U21.IN1B, U$21.EXITCOIL0
unnamed: U21.IN0A, U$21.INCOIL1
unnamed: U21.IN0B, U$21.EXITCOIL1
unnamed: U21.IN2A, U$21.EXITCOIL2B
unnamed: U21.IN2B, U$21.INCOIL2B
unnamed: U21.IN3A, U$21.INCOIL3
unnamed: U21.IN3B, U$21.EXITCOIL3
unnamed: U21.IN1A, U$21.INCOIL0
unnamed: U23.IN1B, U$23.EXITCOIL0
unnamed: U23.IN0A, U$23.INCOIL1
unnamed: U23.IN0B, U$23.EXITCOIL1
unnamed: U23.IN2A, U$23.EXITCOIL2B
unnamed: U23.IN2B, U$23.INCOIL2B
unnamed: U23.IN3A, U$23.INCOIL3
unnamed: U23.IN3B, U$23.EXITCOIL3
unnamed: U23.IN1A, U$23.INCOIL0
unnamed: U25.IN1B, U$25.EXITCOIL0
unnamed: U25.IN0A, U$25.INCOIL1
unnamed: U25.IN0B, U$25.EXITCOIL1
unnamed: U25.IN2A, U$25.EXITCOIL2B
unnamed: U25.IN2B, U$25.INCOIL2B
unnamed: U25.IN3A, U$25.INCOIL3
unnamed: U25.IN3B, U$25.EXITCOIL3
unnamed: U25.IN1A, U$25.INCOIL0
unnamed: U27.IN1B, U$27.EXITCOIL0
unnamed: U27.IN0A, U$27.INCOIL1
unnamed: U27.IN0B, U$27.EXITCOIL1
unnamed: U27.IN2A, U$27.EXITCOIL2B
unnamed: U27.IN2B, U$27.INCOIL2B
unnamed: U27.IN3A, U$27.INCOIL3
unnamed: U27.IN3B, U$27.EXITCOIL3
unnamed: U27.IN1A, U$27.INCOIL0
unnamed: U29.IN1B, U$29.EXITCOIL0
unnamed: U29.IN0A, U$29.INCOIL1
unnamed: U29.IN0B, U$29.EXITCOIL1
unnamed: U29.IN2A, U$29.EXITCOIL2B
unnamed: U29.IN2B, U$29.INCOIL2B
unnamed: U29.IN3A, U$29.INCOIL3
unnamed: U29.IN3B, U$29.EXITCOIL3
unnamed: U29.IN1A, U$29.INCOIL0
unnamed: U31.IN1B, U$31.EXITCOIL0
unnamed: U31.IN0A, U$31.INCOIL1
unnamed: U31.IN0B, U$31.EXITCOIL1
unnamed: U31.IN2A, U$31.EXITCOIL2B
unnamed: U31.IN2B, U$31.INCOIL2B
unnamed: U31.IN3A, U$31.INCOIL3
unnamed: U31.IN3B, U$31.EXITCOIL3
unnamed: U31.IN1A, U$31.INCOIL0
unnamed: U33.IN1B, U$33.EXITCOIL0
unnamed: U33.IN0A, U$33.INCOIL1
unnamed: U33.IN0B, U$33.EXITCOIL1
unnamed: U33.IN2A, U$33.EXITCOIL2B
unnamed: U33.IN2B, U$33.INCOIL2B
unnamed: U33.IN3A, U$33.INCOIL3
unnamed: U33.IN3B, U$33.EXITCOIL3
unnamed: U33.IN1A, U$33.INCOIL0
unnamed: U35.IN1B, U$35.EXITCOIL0
unnamed: U35.IN0A, U$35.INCOIL1
unnamed: U35.IN0B, U$35.EXITCOIL1
unnamed: U35.IN2A, U$35.EXITCOIL2B
unnamed: U35.IN2B, U$35.INCOIL2B
unnamed: U35.IN3A, U$35.INCOIL3
unnamed: U35.IN3B, U$35.EXITCOIL3
unnamed: U35.IN1A, U$35.INCOIL0
unnamed: U37.IN1B, U$37.EXITCOIL0
unnamed: U37.IN0A, U$37.INCOIL1
unnamed: U37.IN0B, U$37.EXITCOIL1
unnamed: U37.IN2A, U$37.EXITCOIL2B
unnamed: U37.IN2B, U$37.INCOIL2B
unnamed: U37.IN3A, U$37.INCOIL3
unnamed: U37.IN3B, U$37.EXITCOIL3
unnamed: U37.IN1A, U$37.INCOIL0
SCL1: PAD14.1, PAD18.1, R5.1, U2.SCL
SCL3: PAD32.1, PAD36.1, R13.1, U4.SCL
SCL4: PAD41.1, PAD45.1, R17.1, U5.SCL
SCL5: PAD50.1, PAD54.1, R21.1, U6.SCL
SCL7: PAD68.1, PAD72.1, R29.1, U8.SCL
SCL8: PAD77.1, PAD81.1, R33.1, U9.SCL
SCL9: PAD86.1, PAD90.1, R37.1, U10.SCL
SCL11: PAD104.1, PAD108.1, R45.1, U12.SCL
SCL13: PAD122.1, PAD126.1, R53.1, U14.SCL
SCL15: PAD140.1, PAD144.1, R61.1, U16.SCL
SCL18: PAD169.1, PAD174.1, R73.1, U19.SCL
SCL20: PAD189.1, PAD194.1, R81.1, U21.SCL
SCL22: PAD209.1, PAD214.1, R89.1, U23.SCL
SCL24: PAD229.1, PAD234.1, R97.1, U25.SCL
SCL26: PAD249.1, PAD254.1, R105.1, U27.SCL
SCL28: PAD269.1, PAD274.1, R113.1, U29.SCL
SCL30: PAD289.1, PAD294.1, R121.1, U31.SCL
SCL32: PAD309.1, PAD314.1, R129.1, U33.SCL
SCL34: PAD329.1, PAD334.1, R137.1, U35.SCL
SCL36: PAD349.1, PAD354.1, R145.1, U37.SCL
SDA1: PAD13.1, PAD17.1, R6.1, U2.SDA
SDA3: PAD31.1, PAD35.1, R14.1, U4.SDA
SDA4: PAD40.1, PAD44.1, R18.1, U5.SDA
SDA5: PAD49.1, PAD53.1, R22.1, U6.SDA
SDA7: PAD67.1, PAD71.1, R30.1, U8.SDA
SDA8: PAD76.1, PAD80.1, R34.1, U9.SDA
SDA9: PAD85.1, PAD89.1, R38.1, U10.SDA
SDA11: PAD103.1, PAD107.1, R46.1, U12.SDA
SDA13: PAD121.1, PAD125.1, R54.1, U14.SDA
SDA15: PAD139.1, PAD143.1, R62.1, U16.SDA
SDA18: PAD168.1, PAD173.1, R74.1, U19.SDA
SDA20: PAD188.1, PAD193.1, R82.1, U21.SDA
SDA22: PAD208.1, PAD213.1, R90.1, U23.SDA
SDA24: PAD228.1, PAD233.1, R98.1, U25.SDA
SDA26: PAD248.1, PAD253.1, R106.1, U27.SDA
SDA28: PAD268.1, PAD273.1, R114.1, U29.SDA
SDA30: PAD288.1, PAD293.1, R122.1, U31.SDA
SDA32: PAD308.1, PAD313.1, R130.1, U33.SDA
SDA34: PAD328.1, PAD333.1, R138.1, U35.SDA
SDA36: PAD348.1, PAD353.1, R146.1, U37.SDA
VDD: C2.1, C4.1, C5.1, C6.1, C8.1, C9.1, C10.1, C12.1, C14.1, C16.1, C19.1, C21.1, C23.1, C25.1, C27.1, C29.1, C31.1, C33.1, C35.1, C37.1, PAD8.1, PAD15.1, PAD28.1, PAD33.1, PAD37.1, PAD42.1, PAD46.1, PAD51.1, PAD64.1, PAD69.1, PAD73.1, PAD78.1, PAD82.1, PAD87.1, PAD100.1, PAD105.1, PAD118.1, PAD123.1, PAD136.1, PAD141.1, PAD165.1, PAD170.1, PAD185.1, PAD190.1, PAD205.1, PAD210.1, PAD225.1, PAD230.1, PAD245.1, PAD250.1, PAD265.1, PAD270.1, PAD285.1, PAD290.1, PAD305.1, PAD310.1, PAD325.1, PAD330.1, PAD345.1, PAD350.1, R5.2, R6.2, R7.2, R13.2, R14.2, R15.2, R17.2, R18.2, R19.2, R21.2, R22.2, R23.2, R29.2, R30.2, R31.2, R33.2, R34.2, R35.2, R37.2, R38.2, R39.2, R45.2, R46.2, R47.2, R53.2, R54.2, R55.2, R61.2, R62.2, R63.2, R73.2, R74.2, R75.2, R81.2, R82.2, R83.2, R89.2, R90.2, R91.2, R97.2, R98.2, R99.2, R105.2, R106.2, R107.2, R113.2, R114.2, R115.2, R121.2, R122.2, R123.2, R129.2, R130.2, R131.2, R137.2, R138.2, R139.2, R145.2, R146.2, R147.2, U2.VDD, U4.VDD, U5.VDD, U6.VDD, U8.VDD, U9.VDD, U10.VDD, U12.VDD, U14.VDD, U16.VDD, U19.VDD, U21.VDD, U23.VDD, U25.VDD, U27.VDD, U29.VDD, U31.VDD, U33.VDD, U35.VDD, U37.VDD

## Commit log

2018-09-25 First fully functional version of the MagBoard 64node code
2018-09-25 MagBoard 16 Node Arduino Code
    Operates on Teensy 3.6 platform
2018-09-25 MagBoard LabVIEW Client
2018-09-25 MagBoard Library - Provides high-level support for interfacing with MagBoard systems
    First commit contains working - but very ugly - code.
    Needs work to refactor functions and tidy everything up!
2018-09-25 MLX90393-Library for low-level communication with the MLX90393 Hall-Effect sensing chip
    First functional version. Not pretty but it works.
2018-09-26 Added Project for LabVIEW Client
2018-09-30 Reconfigured structure of repository to include libraries and support docs
    Updated the repository so that it can track libraries, multiple arduino projects (linked to each MagSense application) and documentation.
    Should be compatible with Arduino Build environment, used the following references:
    https://arduino.stackexchange.com/questions/348/how-to-organize-my-arduino-projects-structure-for-easy-source-control
    https://gitlab.com/mikealger/ExampleArduinoProjectStructure/tree/master/ExampleSketchBook
2018-10-01 Added documentation on electronics files to 16 and 64 node systems
2018-10-03 Updated readmes
2018-10-03 Inclusion of HAILO splint code
    Code added for HAILO splint project
    This code was produced by Belquis Haider as the outcome of her 2018 Internship.
2018-10-05 Draft implementation of asynchronous i2c calls
2018-10-11 Added lightweight matlab interface
2018-10-12 Asynchronous code and removed some copy-paste
    Untested currently, stuff still needs adding to header files. Essentially have replaced blocking i2c with sendRequest. Use bytes.available to see when stuff is good to go in the isReadyFunction then 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
2018-10-18 MagLib: Refactored reading to allow asynchronous reads
    Now each mux is set, followed by a function check to return the correct
    device object pointer; this is rather than using device1, device2...
    Eventually these should actually be moved into an array of objects.
    After finding the device, we can then go ahead and do an asynchrnous
    request for bytes for each wire1,wire2... This is done with the i2c
    sweep variable.
2018-10-18 MLX asynchronous support
    I2C_NOSTOP must be called at various points to keep the bus alive
2018-10-18 benchmark mode and i2c asynch setup
2018-10-18 lightweight matlab interface
2018-10-18 Error handling and single value mux control
2018-10-18 Moved MLX devices into an object array
    Confusingly in the code there were two device objects. The top level one
    was for the board, eg device.read64nodes. There were also private device
    nodes device1,device2,... which reffered to MLX devices. They were
    really _virtual_ anyway because all they did different was contain an
    address and when the mux was changed it actually reffered to a different
    node all together.
2018-10-18 Copyright, which wire, remove magic numbers
    Added copyright notice, same as Pete has used so far (MIT) since code is
    becoming mature and is publically available.
    Now have replaced a lot of the switch-case with a function that returns
    the correct wire object. This allows indexing for neatness.
    Have replaced some of the 'magic numbers' with constants defined in the
    header.
2018-10-19 Comments and simplify takeMeasure with WhichWire
    Working as of comit
2018-10-19 Cleaned up packet offset calculation
2018-10-19 Remove unused ReadMeasurement function
2018-10-19 Cleaned directory tree and removed version numbers
    Git can handle version numbering and so version numbers should not be
    included in file names
2018-10-22 Code revision to support the HAILO splint
    Major update of code to support the HAILO splint -
    1. updated libraries with HAILO specific code (i2C code differs from implementation for Teensy boards with multiple I2C buses).
    2. updated labview client to recieve via Bluetooth and display in graphical form
    This predates recent code optimisation conducted by Chris on the main library for the MagBoard project
2018-12-18 Final updates to LabVIEW client
    Should
2018-12-21 chris finished
    PCBs and code changes as of DEC2018
    Super fast i2c and coil designs as sent off to FS
2019-01-29 File tidy + sort
    Started spring clean of files - no code change
2019-02-04 Update HAILO files to current versions
2019-02-10 Initial commit of Magboard UI Code
    Initial workings of UI codebase for Magboard
    Includes LabVIEW Client and Arduino Code
    Designed to provide command driven interface
    Still WIP!
2019-02-12 Update to MagBoard UI - Basic functionality working
    Now the system has a working LabVIEW client and Arduino master
    - system connection
    - system check
    - streaming over serial (memory leaks....)
2019-02-16 Implemented Bluetooth over Serial
    Basic functionality in place - works through standard Serial port on LabVIEW client
    Arduino code needs tidying with communications functions placed in MagLib library (not main code).
2019-02-28 Added initial version of strain map into LabVIEW Client
    Strain map shows XYZ displacements of nodes
    Work required to tidy and calibrate sensor response
2019-03-13 Update to start integration with SDFat datalogging
2019-03-13 Added initial native BT support
2019-03-15 Native bluetooth fully functional
2019-03-25 Initial Commits to SD logging
2019-04-15 SD Logging example added to repo
    Test SdFAT based datalogging to SD card on the inbuilt Teensy 3.6 card holder.
    works nicely.
2019-04-24 SD card logging and upload complete
    Added full support for logging to SD card
    Arduino code supports logging, upload and testing filesystem
    LabVIEW Client supports all above - with some bug fixes
2019-05-13 Started addition of improved MLX chip configuration
    Adding offsets to Z axis and configuring gains etc
2019-05-15 Initial version of N128 support
2019-05-21 Started progress to N128 code
2019-05-31 Initial NN sensor calibration added
    Integrated NN calibration functions into UI and FileReader
    Calibration files added to project.
    LabVIEW Version currently v2016.
    NB - Future commits will use LabVIEW v2018
2019-09-30 Merged libraries
2019-09-30 Improved documentation.
2019-10-01 Added LabVIEW client apps
2019-10-01 Added basic data visualisation for single node
2019-10-03 Improved streaming/visualisation for single node
2019-10-07 Improved streaming for up to 16 nodes
2019-10-08 Added Brace+ interface function
2019-10-11 Improved documentation
2019-10-11 Added RN4781 interface in Comms menu
2019-10-15 Added error checking for 128 node board tests
2019-10-15 Tidied up documentation
2019-10-16 Added node sweep test file and improved node test function
2019-10-17 Added 128 board node layout details
2019-10-22 Added 128 node magboard file writing tests and corresponding LabVIEW client code
2019-10-23 Improved 128 Node reading, file writing tests and new serial comms interface menu
2019-10-23 Added row scanning footplate data file
2019-10-25 Added optional verbose feedback for chip configuratio
2019-10-29 Improved I2C scan stability and menu interface with Serial
2019-10-31 Integration with LabView 128 node serial monitor
2019-10-31 Added serial timeout function to streaming and removed deprecated const char* functions
2019-10-31 Improved robustness and basic led interface
2019-11-04 Adjusted MLX90393 sensor Gain/Resolution config
2019-11-07 Updated example files
2019-11-07 Fixed bugs for swapping between 64/128 node boards
2019-11-20 Improved HAILO Mux settings
2019-11-27 Added updated LabVIEW code for 128 Node Board Client
2019-11-29 Improved data packet organisation across multiple devices
2019-11-29 Added improved BLE platform for MagLib
2019-12-02 Minor file upload bug fixes
2019-12-11 Finalised Footplate software for CAH Clinical Trials
2019-12-16 Fixed minor bugs, verified code base for both 64 and 128 node magboards
2019-12-18 Finalised MagLib with FootPlate Viewer, Logger and FileIO LabVIEW Clients
2020-01-07 Improved 3D graph and user interface
2020-01-08 Added new NN calibration file and removed minor labview bugs
2020-01-13 Fixed labview file reading bug and added BLE GATT profile
2020-01-15 Improved GUI, added ESCAPES_Main.vi
2020-01-21 Improved LabVIEW client, shortened file write to 1MB
2020-01-24 Added BracePLUS labview client
2020-01-27 Added webcam and VLC functionality, minor UI improvements with file reviewing
2020-01-30 Added updated MagLib library, improved LabVIEW VLC client with automatic render window
2020-02-18 Final webcam + UI improvements
2020-02-21 ESCAPES Trials Code
2020-02-25 Added recorded data
2020-03-27 Fixed MagLib bugs, tested programs for each platform and separated into designated System Program folders
2020-04-16 Updated documentation for MagLib codebase
2020-04-22 Improved brace+ UI
2020-06-29 Added BracePLUS smartphone app
